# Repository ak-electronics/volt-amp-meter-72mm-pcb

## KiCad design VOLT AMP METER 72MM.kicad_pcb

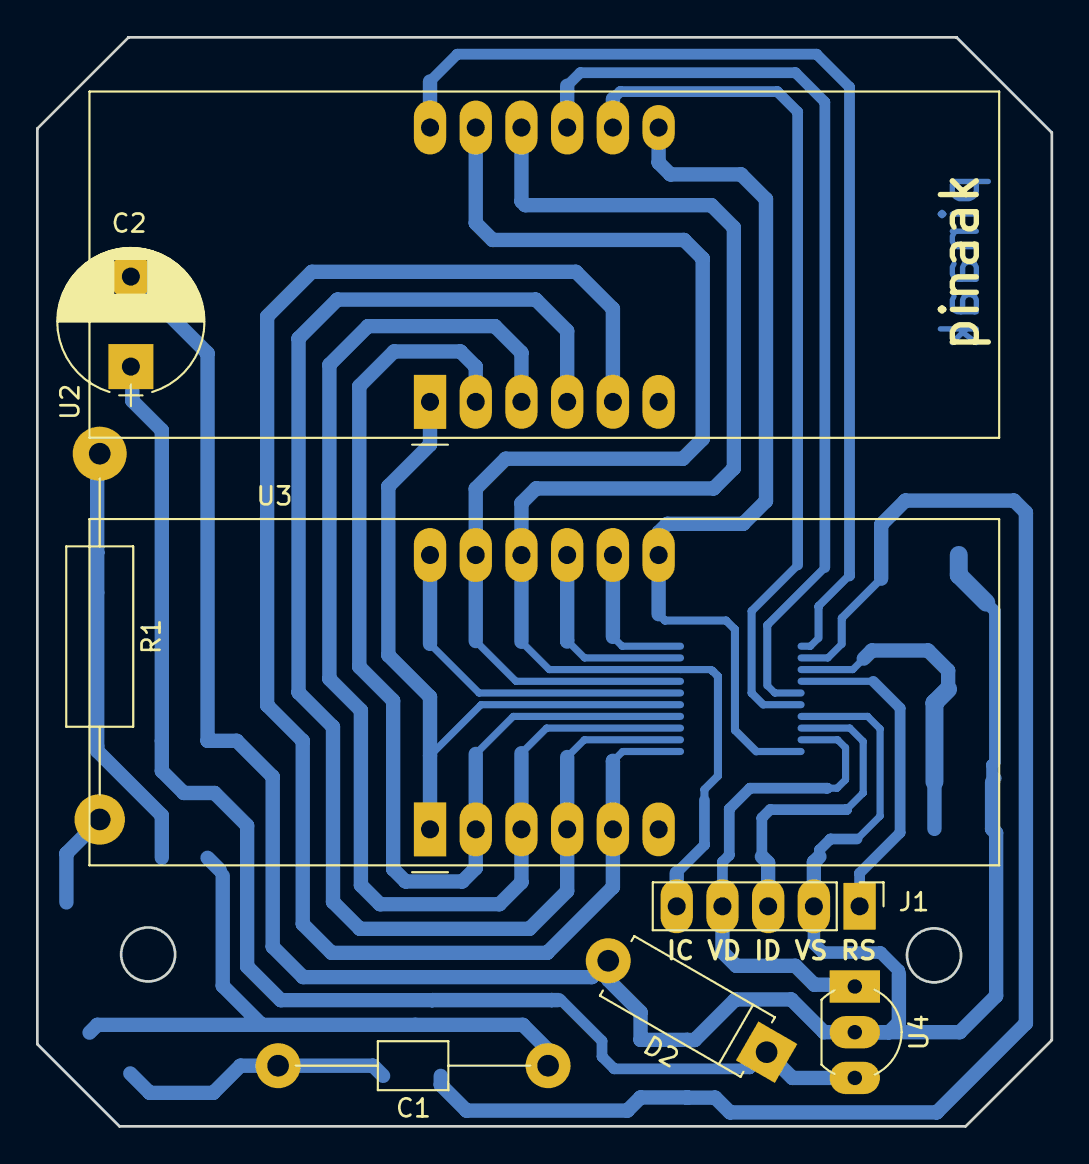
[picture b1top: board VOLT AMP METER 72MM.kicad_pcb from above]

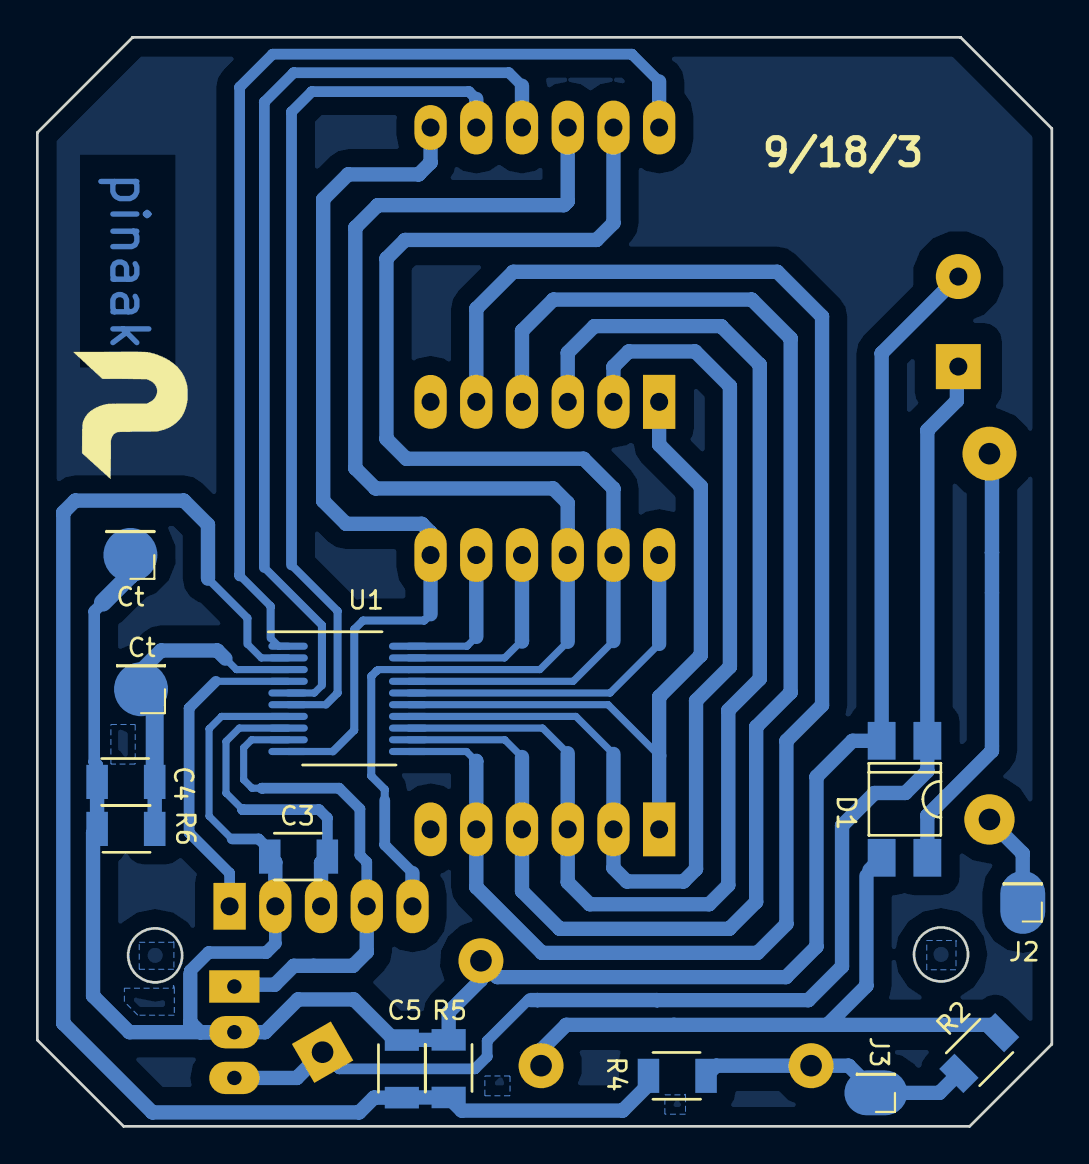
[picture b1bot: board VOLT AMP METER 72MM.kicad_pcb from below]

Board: 2 copper layers, 56.4 x 60.5 mm, 21 parts (13 on the bottom side), 25 nets.

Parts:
C1: 684J; C_Axial_L3.8mm_D2.6mm_P15.00mm_Horizontal
C2: 470uf; CP_Radial_D8.0mm_P5.00mm
C3, C4, C5: C; Resistor_1206
Ct: Conn_01x01; Pin_Header_Straight_1x01_Pitch2.54mm
Ct#2: Conn_01x01; Pin_Header_Straight_1x01_Pitch2.54mm
D1: D_Bridge_+-AA; MB10_bridge
D2: 7.5V; D_5W_P10.16mm_Horizontal
J1: Conn_01x05; Pin_Header_Straight_1x05_Pitch2.54mm
J2, J3: Conn_01x01; Pin_Header_Straight_1x01_Pitch2.00mm
R1: 100R; R_Axial_DIN0411_L9.9mm_D3.6mm_P20.32mm_Horizontal
R2: 470KR; Resistor_1206
R4: 330KR; Resistor_1206
R5: 1.5KR; Resistor_1206
R6: 100R; Resistor_1206
U1: STM8003F3; SSOP-20_custom
U2, U3: CA56-12SYKWA
U4: L78L05_TO92; TO-92_Inline_Wide

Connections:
A: U1.17, U2.11, U3.11
AC_voltage: C5.2, R4.1, R5.2, U1.2
B: U1.10, U2.7, U3.7
C: U1.12, U2.4, U3.4
D: U1.14, U2.2, U3.2
D1: U1.1, U2.12
D2: U1.5, U2.9
D3: U1.6, U2.8
D4: U1.16, U3.12
D5: U1.19, U3.9
D6: U1.20, U3.8
DP: U1.13, U2.3, U3.3
E: U1.15, U2.1, U3.1
F: J1.5, U1.18, U2.10, U3.10
G: U1.11, U2.5, U3.5
NRST: J1.1, U1.4
unnamed: C1.1, D1.4, R2.1
unnamed: C1.2, J3.1, R2.2, R4.2
unnamed: C2.1, D1.1, D2.1, U4.3
unnamed: D1.3, R1.1
unnamed: J2.1, R1.2
VDD: J1.4, U1.9, U4.1
VSS: C2.2, C3.1, C4.2, C5.1, Ct#2.1, D1.2, D2.2, J1.2, R5.1, R6.1, U1.7, U4.2
Vcap: C3.2, J1.3, U1.8
current: C4.1, Ct.1, R6.2, U1.3

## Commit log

2024-12-08 fisrt commit v1.0
